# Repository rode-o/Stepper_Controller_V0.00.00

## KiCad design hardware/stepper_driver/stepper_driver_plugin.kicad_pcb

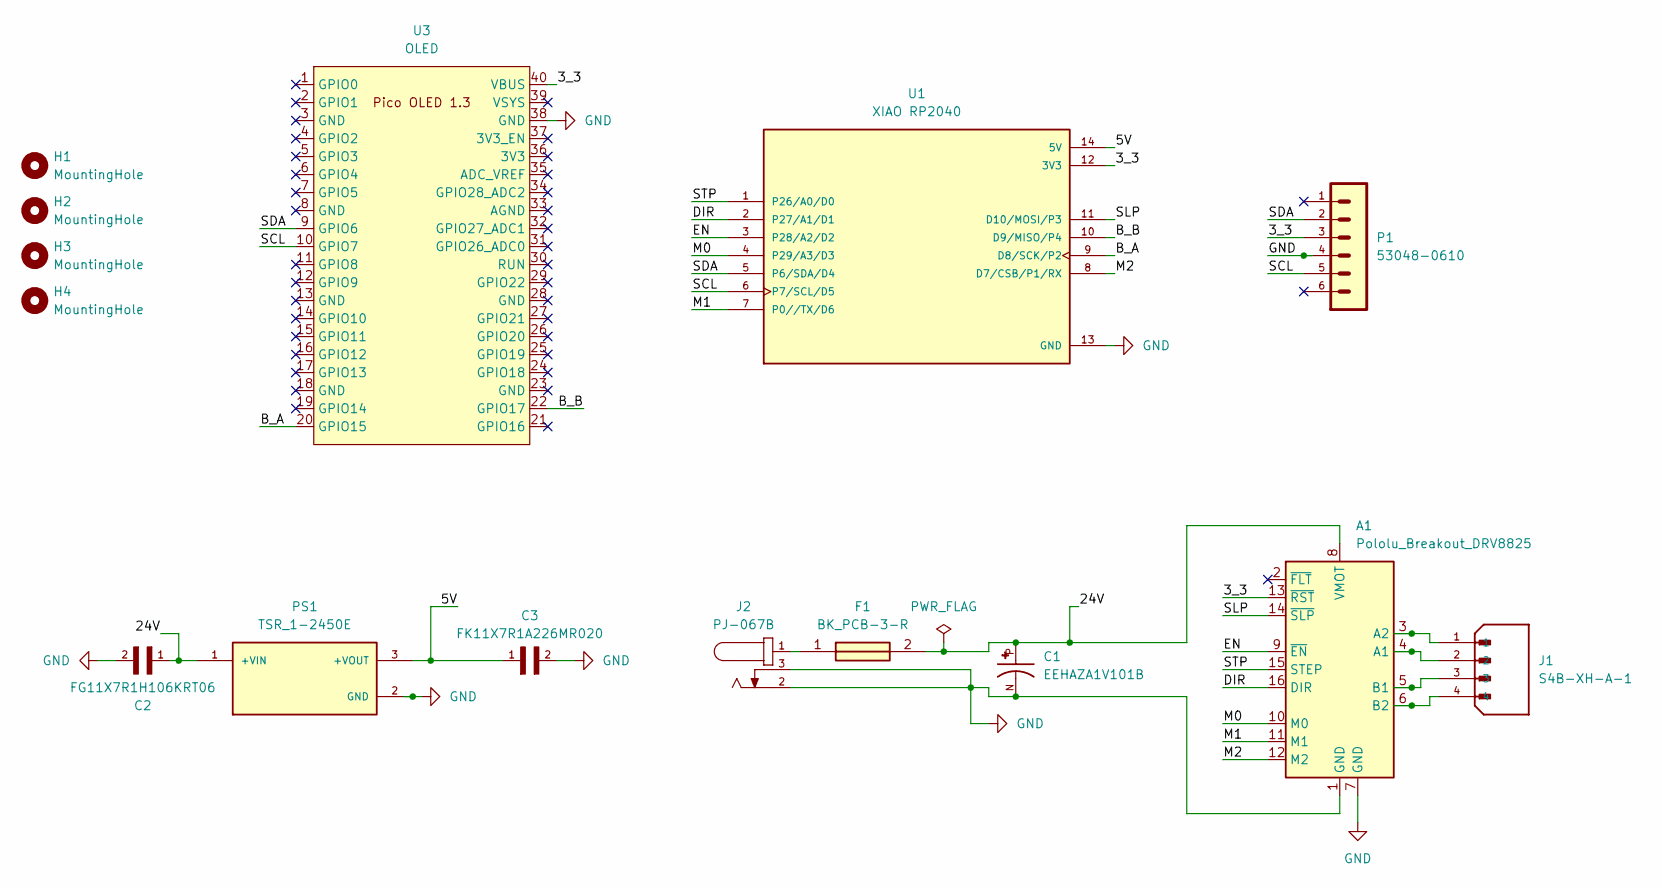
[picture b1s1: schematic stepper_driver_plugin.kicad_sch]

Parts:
A1: Pololu_Breakout_DRV8825; Pololu_Breakout-16_15.2x20.3mm
C1: EEHAZA1V101B; PARTREV 10-MAY-21; DigiKey_Part_Number 10-EEH-AZA1V101BCT-ND
C2: FG11X7R1H106KRT06; CAPRB250W50L550T400H700; PARTREV 20200310; DigiKey_Part_Number 445-173117-1-ND
C3: FK11X7R1A226MR020; CAPRB250W50L550T400H700; PARTREV 20151209; DigiKey_Part_Number 445-8259-ND
F1: BK_PCB-3-R; BKPCB3R; Mouser Part Number 504-BK/PCB-3-R
H1, H2, H3, H4: MountingHole; MountingHole_2.2mm_M2
J1: S4B-XH-A-1; JST_S4B-XH-A-1; PARTREV 27-1-20
J2: PJ-067B; CUI_PJ-067B; PARTREV 1.02
P1: 53048-0610; DigiKey_Part_Number WM1746-ND
PS1: TSR_1-2450E; CONV_TSR_1-2450E; PARTREV May 25, 2020; DigiKey_Part_Number 1951-TSR1-2450E-ND
U1: XIAO RP2040; XIAO-RP2040-DIP; PARTREV 1.3
U3: OLED; RPi_Pico_SMD_TH

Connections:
/3_3: A1.13 (~RST), P1.3, U1.12 (3V3), U3.40 (VBUS)
/5V: C3.1, PS1.3 (+VOUT), U1.14 (5V)
/24V: A1.8 (VMOT), C1.P, C2.1, F1.2, PS1.1 (+VIN)
/B_A: U1.9 (D8/SCK/P2), U3.20 (GPIO15)
/B_B: U1.10 (D9/MISO/P4), U3.22 (GPIO17)
/DIR: A1.16 (DIR), U1.2 (P27/A1/D1)
/EN: A1.9 (~EN), U1.3 (P28/A2/D2)
/M0: A1.10 (M0), U1.4 (P29/A3/D3)
/M1: A1.11 (M1), U1.7 (P0//TX/D6)
/M2: A1.12 (M2), U1.8 (D7/CSB/P1/RX)
/SCL: P1.5, U1.6 (P7/SCL/D5), U3.10 (GPIO7)
/SDA: P1.2, U1.5 (P6/SDA/D4), U3.9 (GPIO6)
/SLP: A1.14 (~SLP), U1.11 (D10/MOSI/P3)
/STP: A1.15 (STEP), U1.1 (P26/A0/D0)
unnamed: A1.4 (A1), J1.2
unnamed: A1.3 (A2), J1.1
unnamed: A1.5 (B1), J1.3
unnamed: A1.6 (B2), J1.4
unnamed: F1.1, J2.1

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
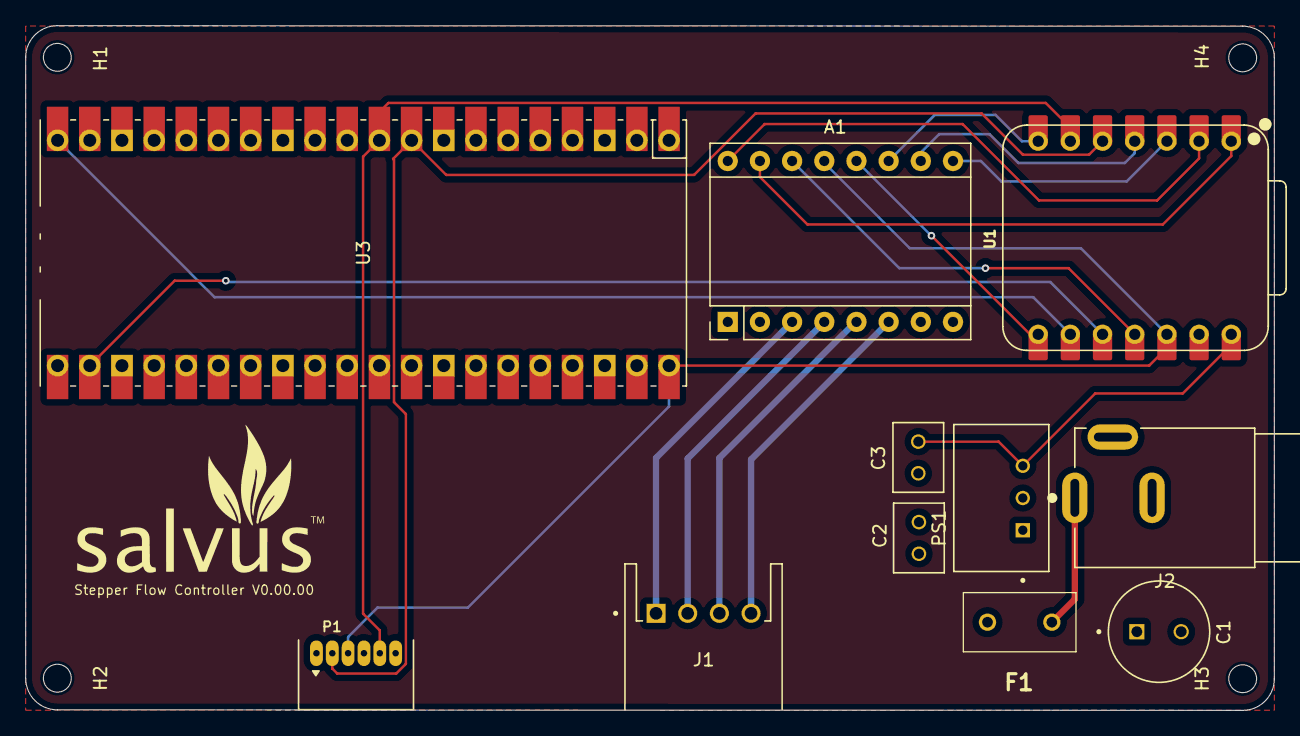
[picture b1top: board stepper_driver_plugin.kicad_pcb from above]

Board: 4 copper layers, 98.6 x 54.0 mm, 15 parts (0 on the bottom side), 20 nets.

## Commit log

2025-06-02 Initial commit: firmware, hardware, KiCad libs, host code, build artifacts
2025-06-23 adding alot, intial firmware included
2025-06-24 added modified srl_mntr
2025-06-29 broken pid, everything else is relatively good
2025-07-02 firmware changes and PCB update
2025-07-06 added srl_cmd and some ui changes - fixed rpm conversion error
2025-07-09 added some flow study script and added volume accum to ui
2025-07-14 added calibration sequence
2025-07-14 added new set_rpm page
